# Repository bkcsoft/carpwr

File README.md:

# CarPWR 
Is a tiny PSU for RPi-based carputers (similar to [Mausberry](http://mausberrycircuits.com/))

## Building
```
make
```

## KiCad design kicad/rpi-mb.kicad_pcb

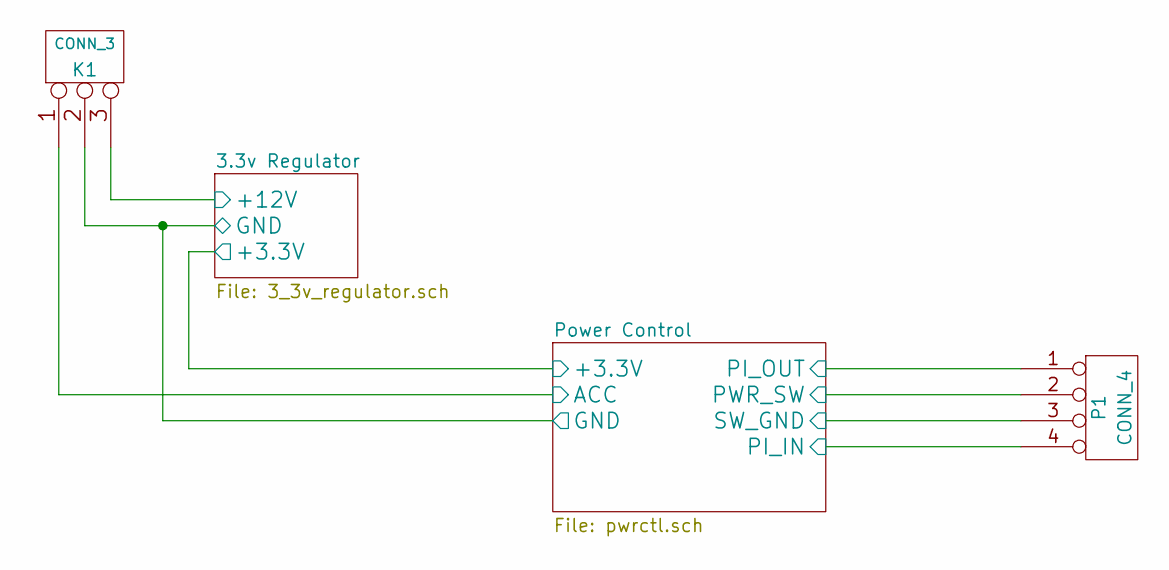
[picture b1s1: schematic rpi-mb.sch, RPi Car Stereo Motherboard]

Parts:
K1: CONN_3
P1: CONN_4

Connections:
/3.3v Regulator/+12V: K1.3; also elsewhere on the board
/3.3v Regulator/GND: K1.2 (PM); also elsewhere on the board
/Power Control/ACC: K1.1; also elsewhere on the board
/Power Control/PI_IN: P1.4; also elsewhere on the board
/Power Control/PI_OUT: P1.1; also elsewhere on the board
/Power Control/PWR_SW: P1.2; also elsewhere on the board
/Power Control/SW_GND: P1.3; also elsewhere on the board

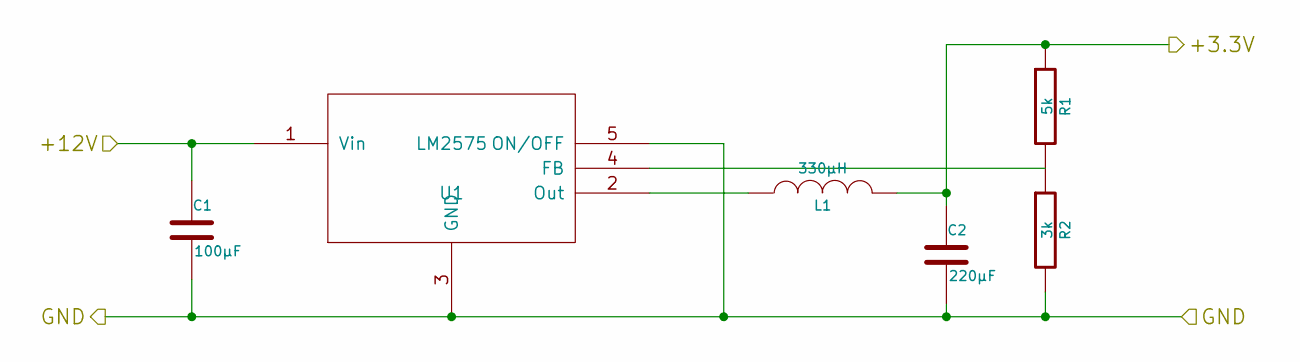
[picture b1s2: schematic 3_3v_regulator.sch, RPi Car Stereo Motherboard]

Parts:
C1: 100µF
C2: 220µF
L1: 330µH
R1: 5k
R2: 3k
U1: LM2575

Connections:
/3.3v Regulator/+3.3V: C2.1, L1.2, R1.1; also elsewhere on the board
/3.3v Regulator/+12V: C1.1, U1.1 (Vin); also elsewhere on the board
/3.3v Regulator/GND: C1.2, C2.2, R2.2, U1.3 (GND), U1.5 (ON/OFF); also elsewhere on the board
unnamed: R1.2, R2.1, U1.4 (FB)
unnamed: L1.1, U1.2 (Out)

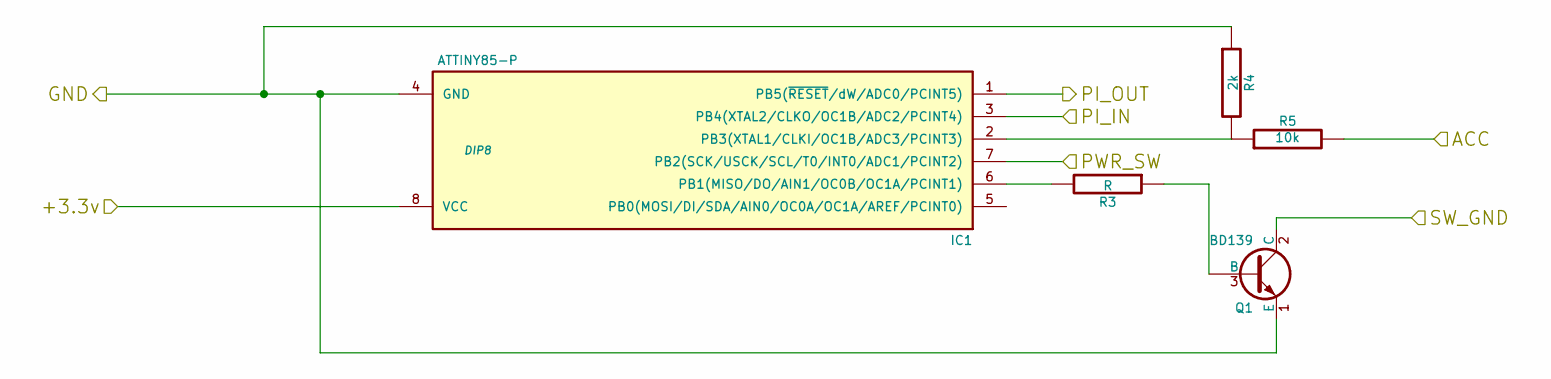
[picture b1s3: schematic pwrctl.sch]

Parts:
IC1: ATTINY85-P; DIP8
Q1: BD139; TO126
R3: R
R4: 2k
R5: 10k

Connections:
/3.3v Regulator/+3.3V: IC1.8 (VCC); also elsewhere on the board
/3.3v Regulator/GND: IC1.4 (GND), Q1.1 (E), R4.1; also elsewhere on the board
/Power Control/ACC: R5.2; also elsewhere on the board
/Power Control/PI_IN: IC1.3 (PB4(XTAL2/CLKO/OC1B/ADC2/PCINT4)); also elsewhere on the board
/Power Control/PI_OUT: IC1.1 (PB5(~RESET~/dW/ADC0/PCINT5)); also elsewhere on the board
/Power Control/PWR_SW: IC1.7 (PB2(SCK/USCK/SCL/T0/INT0/ADC1/PCINT2)); also elsewhere on the board
/Power Control/SW_GND: Q1.2 (C); also elsewhere on the board
unnamed: Q1.3 (B), R3.1
unnamed: IC1.6 (PB1(MISO/DO/AIN1/OC0B/OC1A/PCINT1)), R3.2
unnamed: IC1.2 (PB3(XTAL1/CLKI/OC1B/ADC3/PCINT3)), R4.2, R5.1

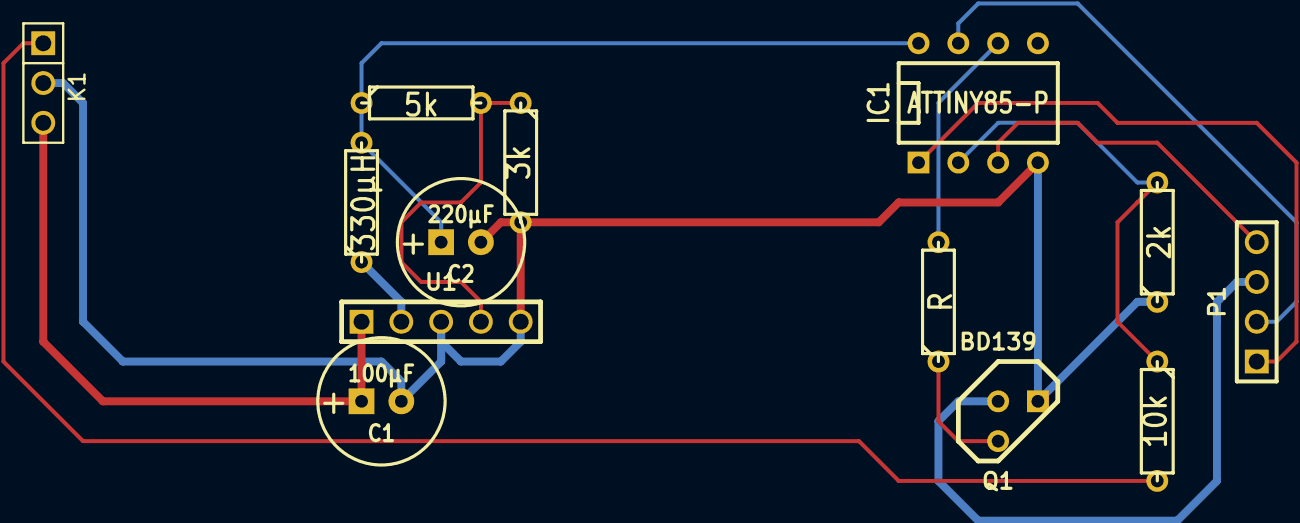
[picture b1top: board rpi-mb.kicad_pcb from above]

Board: 2 copper layers, 13 parts (0 on the bottom side), 13 nets.

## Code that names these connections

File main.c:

#include <avr/io.h>
// F_CPU available from commandline
#include <avr/interrupt.h>
#include <avr/wdt.h>
#include <avr/sleep.h>

#define PIN_ACC    PB3 // Reading ACC-status (High == on, Low == off)
#define PIN_PI_IN  PB4 // RPi says goodnight (High == on, Low == off)
#define PIN_PI_OUT PB5 // Tell RPi goodnight (High == dead, Low == wake)
#define PIN_SW     PB1 // Power-Supply (High == on, Low == off)
#define PIN_PWR    PB2 // Power-button

#define MASK_ACC    (1<<PIN_ACC)
#define MASK_PI_IN  (1<<PIN_PI_IN)
#define MASK_PI_OUT (1<<PIN_PI_OUT)
#define MASK_SW     (1<<PIN_SW)
#define MASK_PWR    (1<<PIN_PWR)

#define DIGIWRITE_H(prt, pn) prt |= (1<<pn)
#define DIGIWRITE_L(prt, pn) prt &= ~(1<<pn)
#define DIGIREAD(prt, pn) (prt | (1<<pn))

#define READ_ACC(x) DIGIREAD(x, PIN_ACC)

#define READ_PI(x) DIGIREAD(x, PIN_PI_IN)
#define PI_ON(x) DIGIWRITE_H(x, PIN_PI_OUT)
#define PI_OFF(x) DIGIWRITE_L(x, PIN_PI_OUT)

#define PS_ON(x) DIGIWRITE_H(x, PIN_SW)
#define PS_OFF(x) DIGIWRITE_L(x, PIN_SW)

#define READ_PWR(x) DIGIREAD(x, PIN_PWR)

void setup() {
	// Setup pins...
	DDRB = 0 | MASK_PI_OUT | MASK_SW;

	// initially set the pins to "low"
	PI_OFF(PORTB);             // RPi dead
	PS_OFF(PORTB);             // Power-Supply off

	// Enable Interrupts
	GIMSK = 1<<PCIE;               // Enable Pin Change Interrupt
	PCMSK = MASK_PI_IN | MASK_ACC | MASK_PWR; // Set PCI-Pins

	set_sleep_mode(SLEEP_MODE_PWR_DOWN);
	sleep_enable();

	sei();
}

// Watchdog Timer Interrupt
// - This function is used to forcibly kill the power
ISR(SIG_WATCHDOG_TIMEOUT) {
	cli();           // Disable Interrupts

	// Disable Watchdog Timer
	wdt_reset();     // Reset WDT
	wdt_disable();   // Disable WDT Completely

	// Turn off RPi and Power-Supply
	PI_OFF(PORTB);
	PS_OFF(PORTB);
}

ISR(SIG_PIN_CHANGE) {
	cli();   // Turn off Interrupts (should be done by libc, but lets do it anyway... 1 cycle more or less ^.^)

	const uint8_t state_mask = MASK_PI_IN | MASK_PWR | MASK_PWR;

	static uint8_t old_state = 0;

	uint8_t masked_state = (PORTB & state_mask);

	// Check mask and de-bounce
	if (masked_state && (masked_state ^ old_state)) {
		const uint8_t new_state = masked_state ^ old_state;
		// ACC turned off
		if (!READ_ACC(new_state)) {
			PI_OFF(PORTB);             // Tell the RPi that it should turn off...
		}
		// ACC turned on
		if (READ_ACC(new_state)) {
			PS_ON(PORTB);
			PI_ON(PORTB);
		}

		// RPi turned off
		if (!READ_PI(new_state)) {
			WDTCR = (1<<WDIE) | (1<<WDE);  // Enable Watchdog Timer Interrupt
			wdt_enable(WDTO_2S);           // Enable WDT set to 2 seconds
		}

		// Pressing the Power-button!
		if (READ_PWR(new_state)) {
			if(READ_PI(PORTB)) { // RPi is on...
				WDTCR = (1<<WDIE) | (1<<WDE);  // Enable Watchdog Timer Interrupt
				wdt_enable(WDTO_4S);           // Enable WDT set to 4 seconds
			} else { // Turn it on :D
				PI_ON(PORTB);          // Tell RPi it's okey to stay on
				PS_ON(PORTB);          // Turn on Power-Supply
			}
		}
		// Released the Power-button!
		if (!READ_PWR(new_state)) {
			wdt_disable();          // Disable the Watchdog Timer Interrupt
			PI_OFF(PORTB);          // Power-Off normally
		}

		old_state = old_state | new_state; // set new old state :D
	}
}


int main(void) {
	setup();

	for(;;){
		sei();
		sleep_cpu();
	}

	return 0;   /* never reached */
}

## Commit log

2016-03-05 Holy fuck this is ugly xD
2016-03-05 Cleaner...
2016-03-05 better makefile
2016-03-05 Now with more interrupts \o/
2016-03-05 no need for the delay-functions anymore
2016-03-05 TABSgit add main.c !
2016-03-05 don't need to enable interrupts in the interrupt
2016-03-05 Now you can turn on the RPi xD (and comment-fix)
2016-03-05 now anything actually works... and removed cruft
2016-03-07 don't track obj/bin-folders
2016-03-10 Actually working ^.^ (And some cleanup...)
2016-03-11 stupid comments
2016-03-23 kicad files added
2018-02-19 Make avr docker-image configurable
2018-02-19 make Makefile CI compatible
2018-02-24 flip pwr-relay and -button output
